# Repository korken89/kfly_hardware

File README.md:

# KFly v3 hardware

This is the hardware for https://github.com/korken89/kfly_firmware

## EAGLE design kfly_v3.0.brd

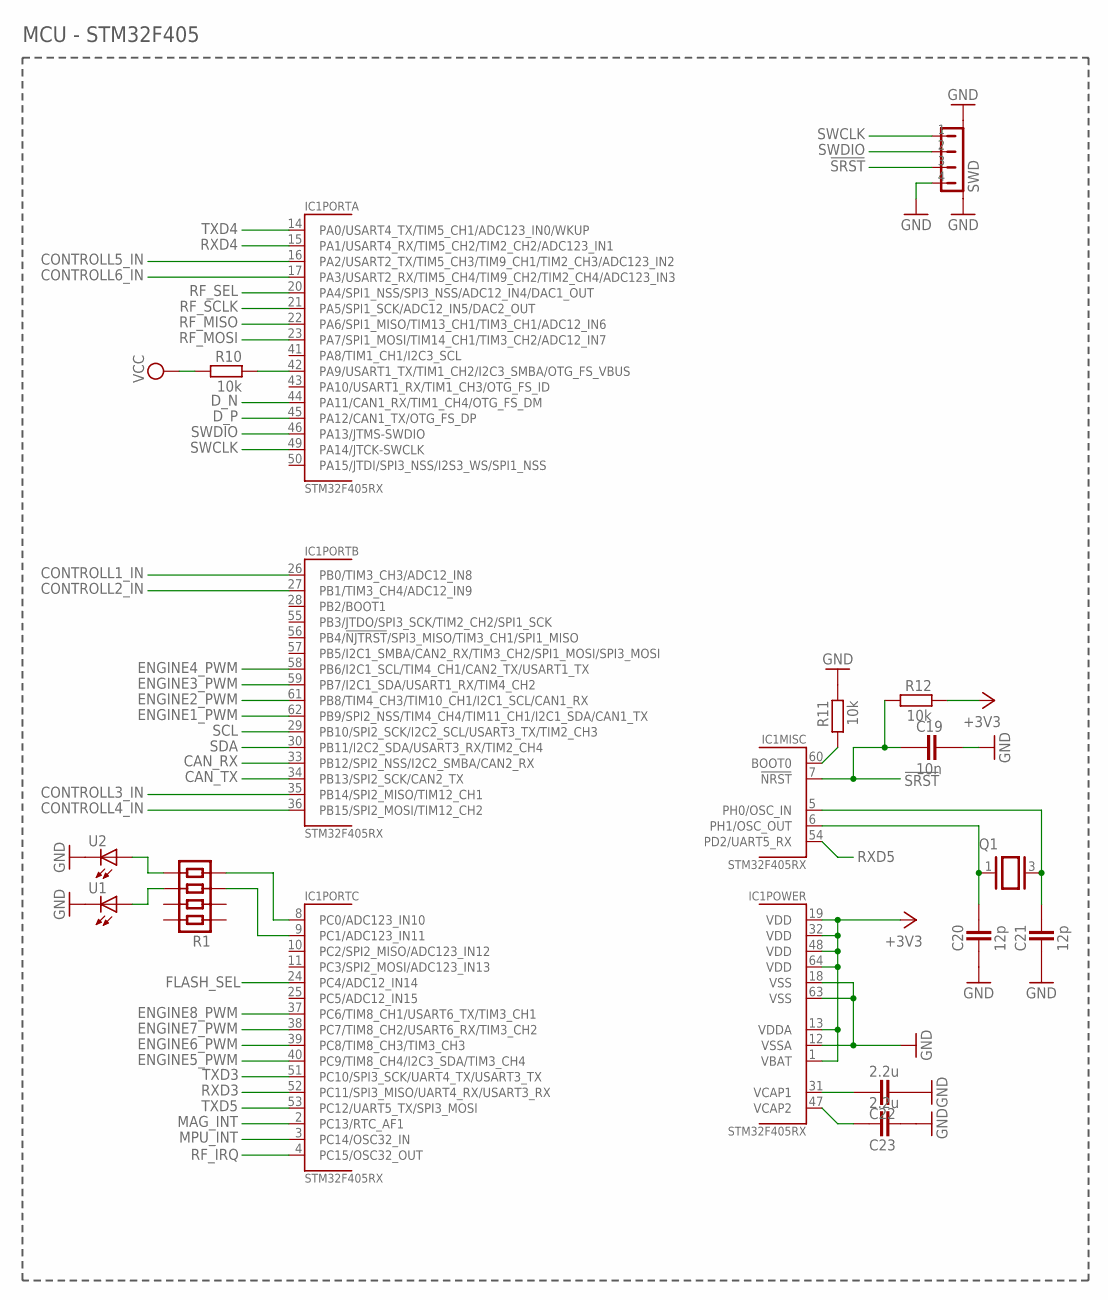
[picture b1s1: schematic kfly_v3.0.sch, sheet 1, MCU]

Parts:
C19: 10n; CAPC1005X60N
C20, C21: 12p; CAPC1005X60N
C22, C23: 2.2u; CAPC1608X92N
IC1: STM32F405RX; LQFP64-10X10
Q1: 2.5X3.2CRYSTAL
R1: RESISTOR-4ARRAY-0804; RESISTORARRAY_0804
R10, R11, R12: 10k; RESC1005X40AN
SWD: JST-4PIN-SIDE-1.0; JST-4PIN-SIDE
U1, U2: LED0603; LED-0603

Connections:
!SRST: C19.1, IC1.7 (!NRST!), R12.2, SWD.3
+3V3: IC1.1 (VBAT), IC1.13 (VDDA), IC1.19 (VDD), IC1.32 (VDD), IC1.48 (VDD), IC1.64 (VDD), R12.1; also elsewhere on the board
CAN_RX: IC1.33 (PB12/SPI2_NSS/I2C2_SMBA/CAN2_RX); also elsewhere on the board
CAN_TX: IC1.34 (PB13/SPI2_SCK/CAN2_TX); also elsewhere on the board
CONTROLL1_IN: IC1.26 (PB0/TIM3_CH3/ADC12_IN8); also elsewhere on the board
CONTROLL2_IN: IC1.27 (PB1/TIM3_CH4/ADC12_IN9); also elsewhere on the board
CONTROLL3_IN: IC1.35 (PB14/SPI2_MISO/TIM12_CH1); also elsewhere on the board
CONTROLL4_IN: IC1.36 (PB15/SPI2_MOSI/TIM12_CH2); also elsewhere on the board
CONTROLL5_IN: IC1.16 (PA2/USART2_TX/TIM5_CH3/TIM9_CH1/TIM2_CH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); also elsewhere on the board
CONTROLL6_IN: IC1.17 (PA3/USART2_RX/TIM5_CH4/TIM9_CH2/TIM2_CH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); also elsewhere on the board
D_N: IC1.44 (PA11/CAN1_RX/TIM1_CH4/OTG_FS_DM); also elsewhere on the board
D_P: IC1.45 (PA12/CAN1_TX/OTG_FS_DP); also elsewhere on the board
ENGINE1_PWM: IC1.62 (PB9/SPI2_NSS/TIM4_CH4/TIM11_CH1/I2C1_SD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); also elsewhere on the board
ENGINE2_PWM: IC1.61 (PB8/TIM4_CH3/TIM10_CH1/I2C1_SCL/CAN1_RX); also elsewhere on the board
ENGINE3_PWM: IC1.59 (PB7/I2C1_SDA/USART1_RX/TIM4_CH2); also elsewhere on the board
ENGINE4_PWM: IC1.58 (PB6/I2C1_SCL/TIM4_CH1/CAN2_TX/USART1_TX); also elsewhere on the board
ENGINE5_PWM: IC1.40 (PC9/TIM8_CH4/I2C3_SDA/TIM3_CH4); also elsewhere on the board
ENGINE6_PWM: IC1.39 (PC8/TIM8_CH3/TIM3_CH3); also elsewhere on the board
ENGINE7_PWM: IC1.38 (PC7/TIM8_CH2/USART6_RX/TIM3_CH2); also elsewhere on the board
ENGINE8_PWM: IC1.37 (PC6/TIM8_CH1/USART6_TX/TIM3_CH1); also elsewhere on the board
FLASH_SEL: IC1.24 (PC4/ADC12_IN14); also elsewhere on the board
GND: C19.2, C20.1, C21.1, C22.2, C23.2, IC1.12 (VSSA), IC1.18 (VSS), IC1.63 (VSS), R11.1, SWD.4, SWD.NC1 (P1), SWD.NC2 (P2), U1.C, U2.C; also elsewhere on the board
MAG_INT: IC1.2 (PC13/RTC_AF1); also elsewhere on the board
MPU_INT: IC1.3 (PC14/OSC32_IN); also elsewhere on the board
unnamed: R1.5, U2.A
unnamed: R1.6, U1.A
unnamed: IC1.60 (BOOT0), R11.2
unnamed: IC1.8 (PC0/ADC123_IN10), R1.4
unnamed: IC1.9 (PC1/ADC123_IN11), R1.3
unnamed: C20.2, IC1.6 (PH1/OSC_OUT), Q1.1
unnamed: C21.2, IC1.5 (PH0/OSC_IN), Q1.3 (2)
unnamed: IC1.42 (PA9/USART1_TX/TIM1_CH2/I2C3_SMBA/OTG_FS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), R10.1
unnamed: C22.1, IC1.31 (VCAP1)
unnamed: C23.1, IC1.47 (VCAP2)
RF_IRQ: IC1.4 (PC15/OSC32_OUT); also elsewhere on the board
RF_MISO: IC1.22 (PA6/SPI1_MISO/TIM13_CH1/TIM3_CH1/ADC12_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); also elsewhere on the board
RF_MOSI: IC1.23 (PA7/SPI1_MOSI/TIM14_CH1/TIM3_CH2/ADC12_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); also elsewhere on the board
RF_SCLK: IC1.21 (PA5/SPI1_SCK/ADC12_IN5/DAC2_OUT); also elsewhere on the board
RF_SEL: IC1.20 (PA4/SPI1_NSS/SPI3_NSS/ADC12_IN4/DAC1_OUT); also elsewhere on the board
RXD3: IC1.52 (PC11/SPI3_MISO/UART4_RX/USART3_RX); also elsewhere on the board
RXD4: IC1.15 (PA1/USART4_RX/TIM5_CH2/TIM2_CH2/ADC123_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); also elsewhere on the board
RXD5: IC1.54 (PD2/UART5_RX); also elsewhere on the board
SCL: IC1.29 (PB10/SPI2_SCK/I2C2_SCL/USART3_TX/TIM2_C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); also elsewhere on the board
SDA: IC1.30 (PB11/I2C2_SDA/USART3_RX/TIM2_CH4); also elsewhere on the board
SWCLK: IC1.49 (PA14/JTCK-SWCLK), SWD.1
SWDIO: IC1.46 (PA13/JTMS-SWDIO), SWD.2
TXD3: IC1.51 (PC10/SPI3_SCK/UART4_TX/USART3_TX); also elsewhere on the board
TXD4: IC1.14 (PA0/USART4_TX/TIM5_CH1/ADC123_IN0/WKUP); also elsewhere on the board
TXD5: IC1.53 (PC12/UART5_TX/SPI3_MOSI); also elsewhere on the board
VCC: R10.2; also elsewhere on the board

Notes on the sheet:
MCU - STM32F405

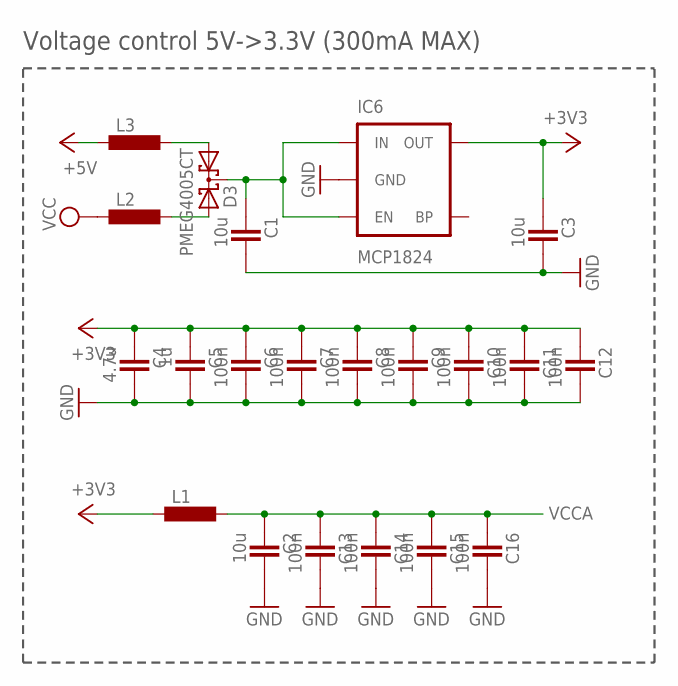
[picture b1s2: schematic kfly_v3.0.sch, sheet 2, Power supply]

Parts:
C1, C2, C3: 10u; CAPC1608X92N
C4: 4.7u; CAPC1608X92N
C5: 1u; CAPC1608X92N
C6, C7, C8, C9, C10, C11, C12, C13, C14, C15, C16: 100n; CAPC1005X60N
D3: PMEG4005CT; SOT23
IC6: MCP1824; SOT23-5
L1, L2, L3: INDUCTOR_0603; INDC1608X95N

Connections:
+3V3: C3.1, C4.1, C5.1, C6.1, C7.1, C8.1, C9.1, C10.1, C11.1, C12.1, IC6.5 (OUT), L1.1; also elsewhere on the board
+5V: L3.1; also elsewhere on the board
GND: C1.2, C2.2, C3.2, C4.2, C5.2, C6.2, C7.2, C8.2, C9.2, C10.2, C11.2, C12.2, C13.2, C14.2, C15.2, C16.2, IC6.2 (GND); also elsewhere on the board
unnamed: D3.2 (A2), L2.2
unnamed: D3.1 (A1), L3.2
VCC: L2.1; also elsewhere on the board
VCCA: C2.1, C13.1, C14.1, C15.1, C16.1, L1.2; also elsewhere on the board
V_RC: C1.1, D3.3 (C), IC6.1 (IN), IC6.3 (EN)

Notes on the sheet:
Voltage control 5V->3.3V (300mA MAX)

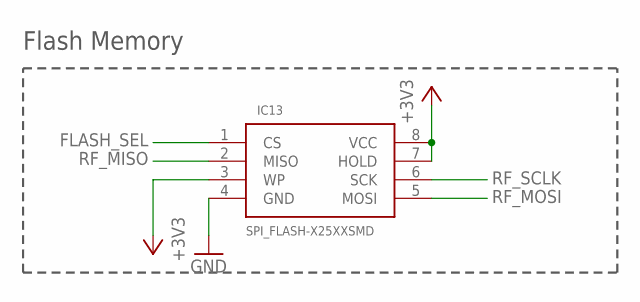
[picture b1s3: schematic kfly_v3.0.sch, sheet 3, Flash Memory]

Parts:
IC13: SPI_FLASH-X25XXSMD; SO08

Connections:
+3V3: IC13.3 (WP), IC13.7 (HOLD), IC13.8 (VCC); also elsewhere on the board
FLASH_SEL: IC13.1 (CS); also elsewhere on the board
GND: IC13.4 (GND); also elsewhere on the board
RF_MISO: IC13.2 (MISO); also elsewhere on the board
RF_MOSI: IC13.5 (MOSI); also elsewhere on the board
RF_SCLK: IC13.6 (SCK); also elsewhere on the board

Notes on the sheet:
Flash Memory

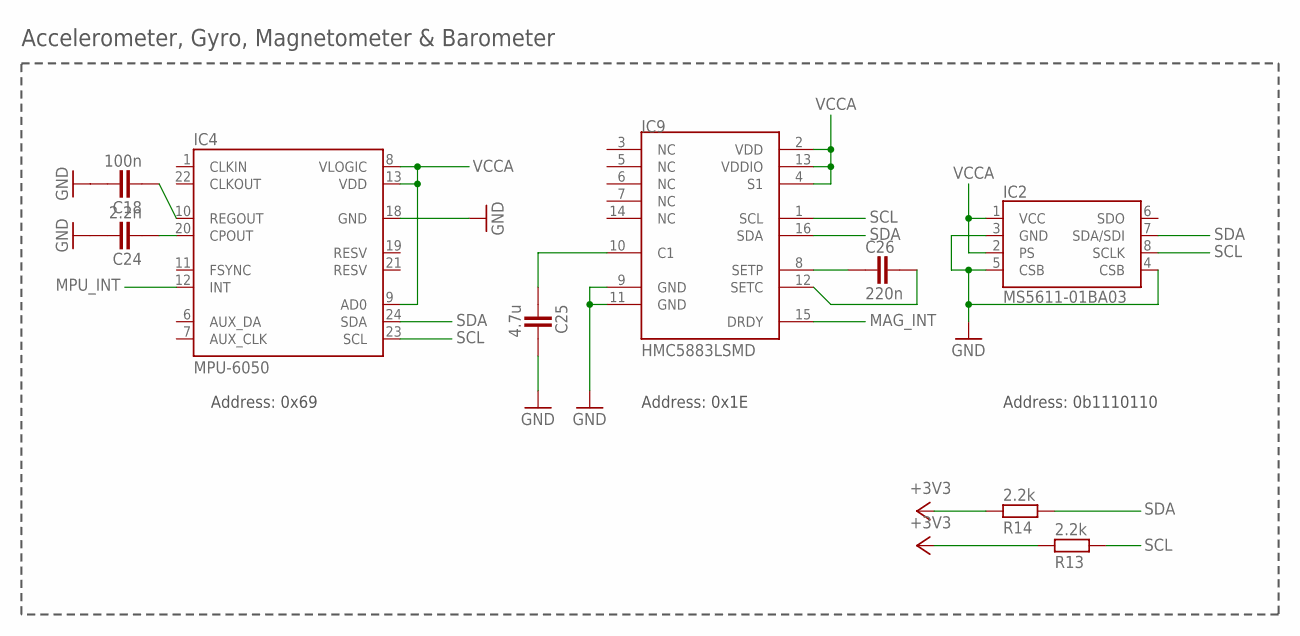
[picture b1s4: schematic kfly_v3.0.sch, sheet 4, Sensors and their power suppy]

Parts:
C18: 100n; CAPC1005X60N
C24: 2.2n; CAPC1005X60N
C25: 4.7u; CAPC1608X92N
C26: 220n; CAPC1608X92N
IC2: MS5611-01BA03; MS5611
IC4: MPU-6050; QFN-24
IC9: HMC5883LSMD; 16LPCC
R13, R14: 2.2k; RESC1005X40AN

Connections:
+3V3: R13.1, R14.1; also elsewhere on the board
GND: C18.2, C24.2, C25.2, IC2.3 (GND), IC2.4 (CSB), IC2.5 (CSB), IC4.18 (GND), IC9.9 (GND), IC9.11 (GND); also elsewhere on the board
MAG_INT: IC9.15 (DRDY); also elsewhere on the board
MPU_INT: IC4.12 (INT); also elsewhere on the board
unnamed: C25.1, IC9.10 (C1)
unnamed: C26.1, IC9.8 (SETP)
unnamed: C26.2, IC9.12 (SETC)
unnamed: C18.1, IC4.10 (REGOUT)
unnamed: C24.1, IC4.20 (CPOUT)
SCL: IC2.8 (SCLK), IC4.23 (SCL), IC9.1 (SCL), R13.2; also elsewhere on the board
SDA: IC2.7 (SDA/SDI), IC4.24 (SDA), IC9.16 (SDA), R14.2; also elsewhere on the board
VCCA: IC2.1 (VCC), IC2.2 (PS), IC4.8 (VLOGIC), IC4.9 (AD0), IC4.13 (VDD), IC9.2 (VDD), IC9.4 (S1), IC9.13 (VDDIO); also elsewhere on the board

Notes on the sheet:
Accelerometer, Gyro, Magnetometer & Barometer
Address: 0x69
Address: 0x1E
Address: 0b1110110

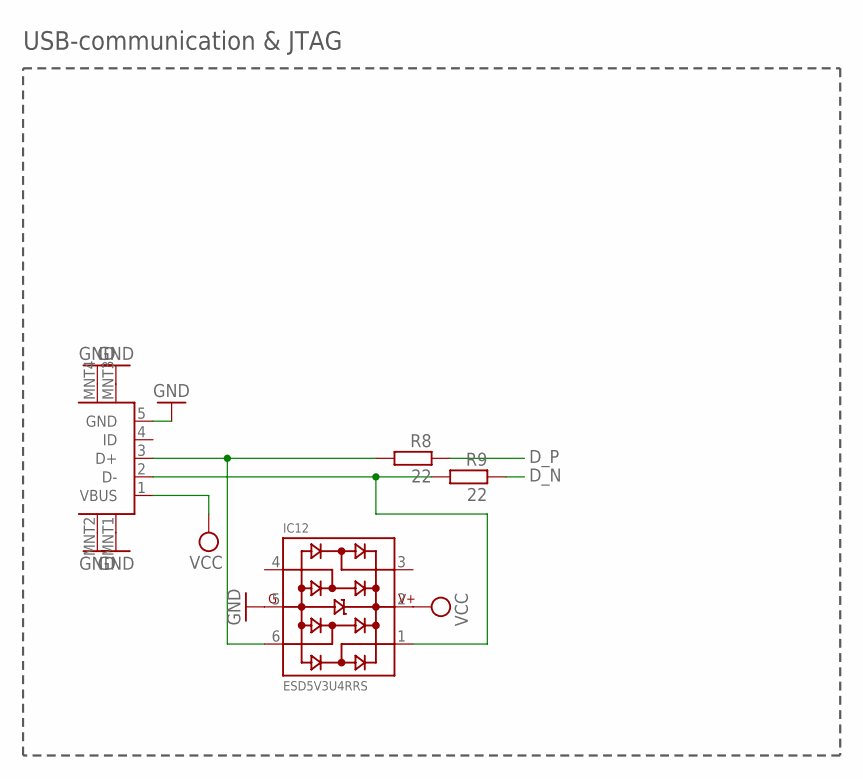
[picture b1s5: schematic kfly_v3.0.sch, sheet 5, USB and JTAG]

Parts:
IC12: ESD5V3U4RRS; SOT363
R8, R9: 22; RESC1005X40AN
USB1: USB-MICRO-B-BOTTOM; MICROUSB_TYPEB_SURFACE

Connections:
D_N: R9.1; also elsewhere on the board
D_P: R8.1; also elsewhere on the board
GND: IC12.5, USB1.5 (GND), USB1.MNT1 (MTN1), USB1.MNT2 (MTN2), USB1.MNT3 (MTN3), USB1.MNT4 (MTN4); also elsewhere on the board
unnamed: IC12.6, R8.2, USB1.3 (D+)
unnamed: IC12.1, R9.2, USB1.2 (D-)
VCC: IC12.2, USB1.1 (VBUS); also elsewhere on the board

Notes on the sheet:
USB-communication & JTAG

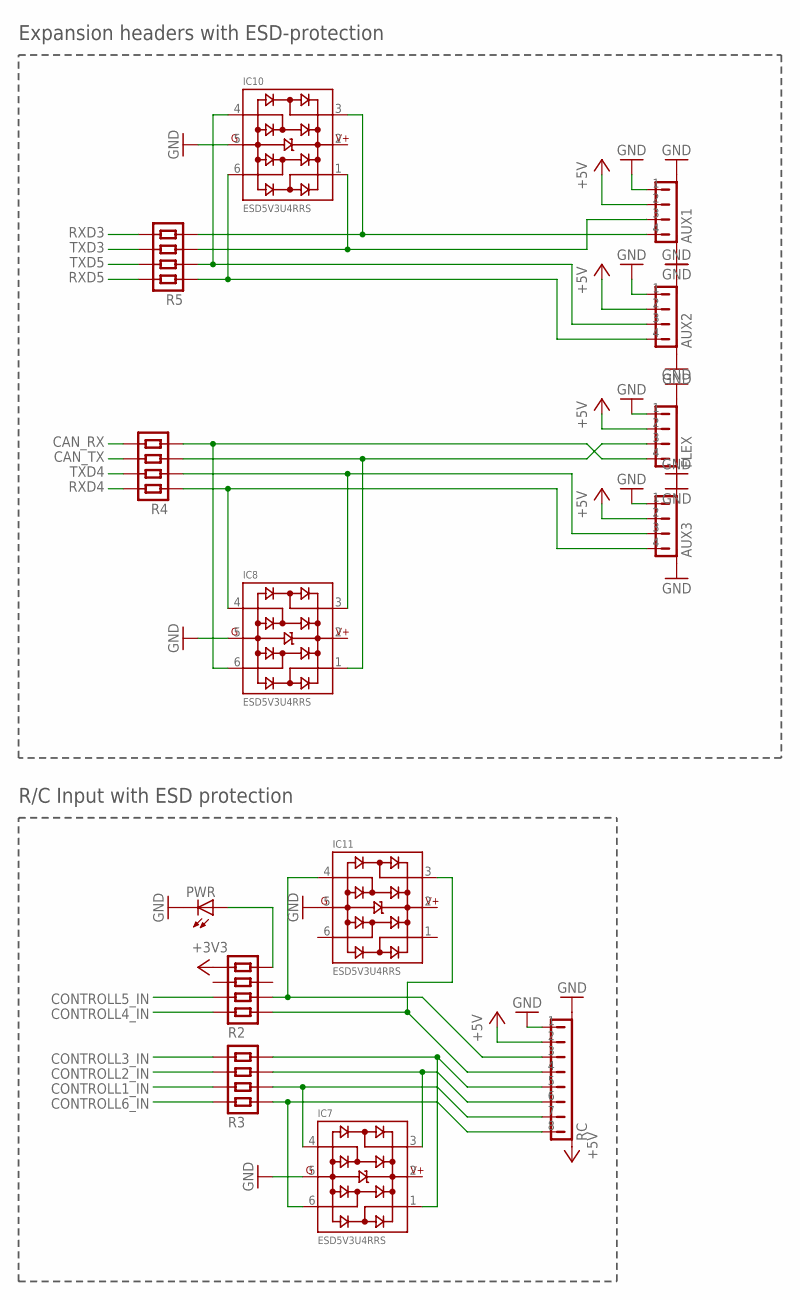
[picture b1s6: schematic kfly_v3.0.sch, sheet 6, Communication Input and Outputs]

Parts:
AUX1, AUX2, AUX3: JST-4PIN-SIDE-1.0; JST-4PIN-SIDE
FLEX: JST-4PIN-SIDE-1.0; JST-4PIN-SIDE
IC7, IC8, IC10, IC11: ESD5V3U4RRS; SOT363
PWR: LED0603; LED-0603
R2, R3, R4, R5: RESISTOR-4ARRAY-0804; RESISTORARRAY_0804
RC: JST-8PIN-SIDE-1.0; JST-8PIN-SIDE

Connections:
+3V3: R2.4; also elsewhere on the board
+5V: AUX1.2, AUX2.2, AUX3.2, FLEX.2, RC.2, RC.NC2 (GND2); also elsewhere on the board
CAN_RX: R4.5; also elsewhere on the board
CAN_TX: R4.6; also elsewhere on the board
CONTROLL1_IN: R3.2; also elsewhere on the board
CONTROLL2_IN: R3.3; also elsewhere on the board
CONTROLL3_IN: R3.4; also elsewhere on the board
CONTROLL4_IN: R2.1; also elsewhere on the board
CONTROLL5_IN: R2.2; also elsewhere on the board
CONTROLL6_IN: R3.1; also elsewhere on the board
GND: AUX1.1, AUX1.NC1 (P1), AUX1.NC2 (P2), AUX2.1, AUX2.NC1 (P1), AUX2.NC2 (P2), AUX3.1, AUX3.NC1 (P1), AUX3.NC2 (P2), FLEX.1, FLEX.NC1 (P1), FLEX.NC2 (P2), IC7.5, IC8.5, IC10.5, IC11.5, PWR.C, RC.1, RC.NC1 (GND1); also elsewhere on the board
unnamed: AUX2.3, IC10.4, R5.2
unnamed: PWR.A, R2.5
unnamed: IC11.4, R2.7, RC.3
unnamed: IC7.6, R3.8, RC.8
unnamed: IC7.1, R3.5, RC.5
unnamed: FLEX.4, IC8.6, R4.4
unnamed: FLEX.3, IC8.1, R4.3
unnamed: AUX2.4, IC10.6, R5.1
unnamed: IC11.3, R2.8, RC.4
unnamed: IC7.3, R3.6, RC.6
unnamed: AUX1.4, IC10.3, R5.4
unnamed: AUX1.3, IC10.1, R5.3
unnamed: AUX3.4, IC8.4, R4.1
unnamed: AUX3.3, IC8.3, R4.2
unnamed: IC7.4, R3.7, RC.7
RXD3: R5.5; also elsewhere on the board
RXD4: R4.8; also elsewhere on the board
RXD5: R5.8; also elsewhere on the board
TXD3: R5.6; also elsewhere on the board
TXD4: R4.7; also elsewhere on the board
TXD5: R5.7; also elsewhere on the board

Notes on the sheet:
Expansion headers with ESD-protection
R/C Input with ESD protection

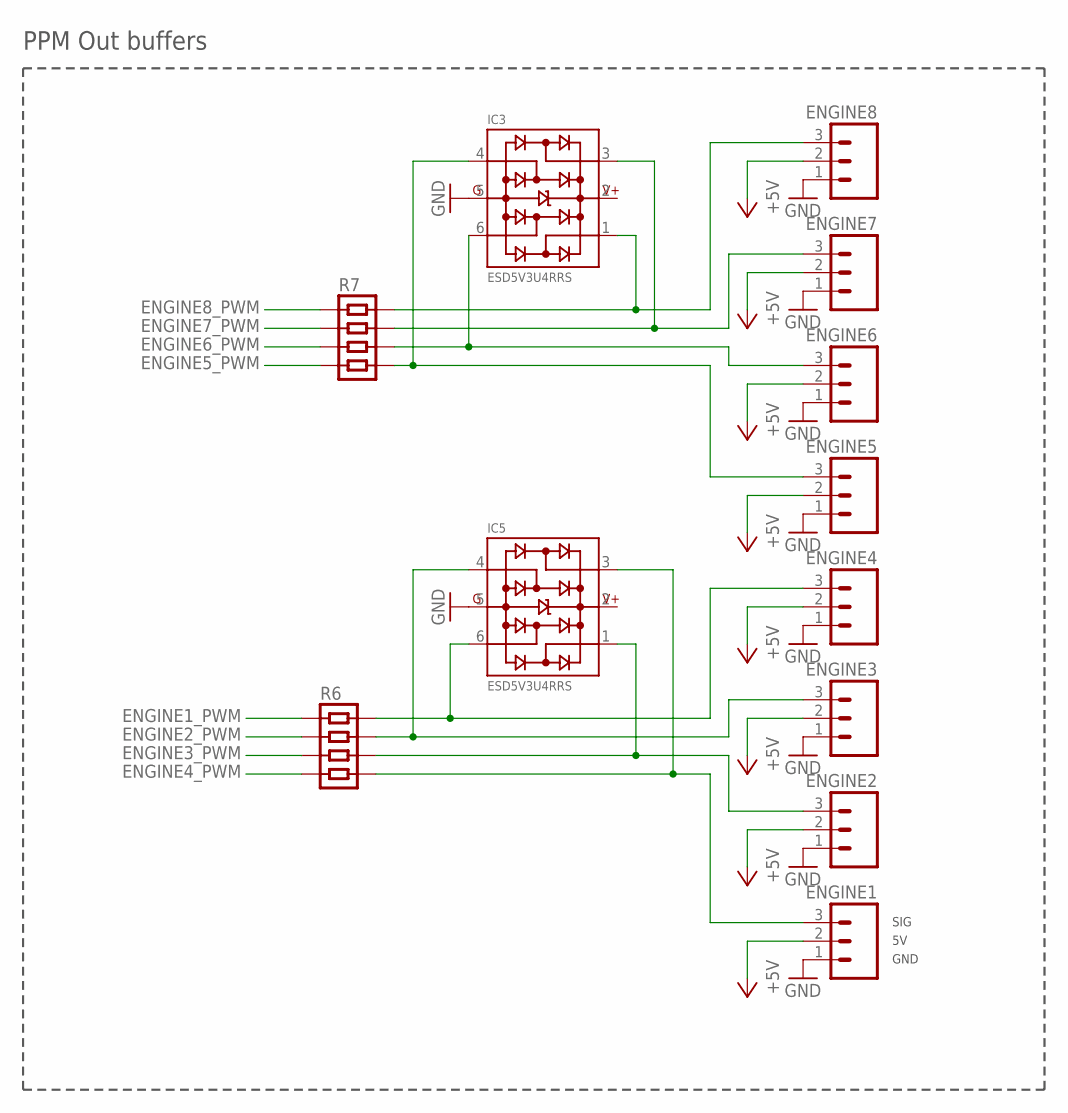
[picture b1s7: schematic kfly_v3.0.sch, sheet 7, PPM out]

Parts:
ENGINE1, ENGINE2, ENGINE3, ENGINE4, ENGINE5, ENGINE6, ENGINE7, ENGINE8: M03
IC3, IC5: ESD5V3U4RRS; SOT363
R6, R7: RESISTOR-4ARRAY-0804; RESISTORARRAY_0804

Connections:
+5V: ENGINE1.2, ENGINE2.2, ENGINE3.2, ENGINE4.2, ENGINE5.2, ENGINE6.2, ENGINE7.2, ENGINE8.2; also elsewhere on the board
ENGINE1_PWM: R6.1; also elsewhere on the board
ENGINE2_PWM: R6.2; also elsewhere on the board
ENGINE3_PWM: R6.3; also elsewhere on the board
ENGINE4_PWM: R6.4; also elsewhere on the board
ENGINE5_PWM: R7.4; also elsewhere on the board
ENGINE6_PWM: R7.3; also elsewhere on the board
ENGINE7_PWM: R7.2; also elsewhere on the board
ENGINE8_PWM: R7.1; also elsewhere on the board
GND: ENGINE1.1, ENGINE2.1, ENGINE3.1, ENGINE4.1, ENGINE5.1, ENGINE6.1, ENGINE7.1, ENGINE8.1, IC3.5, IC5.5; also elsewhere on the board
unnamed: ENGINE8.3, IC3.1, R7.8
unnamed: ENGINE7.3, IC3.3, R7.7
unnamed: ENGINE6.3, IC3.6, R7.6
unnamed: ENGINE5.3, IC3.4, R7.5
unnamed: ENGINE2.3, IC5.1, R6.6
unnamed: ENGINE1.3, IC5.3, R6.5
unnamed: ENGINE4.3, IC5.6, R6.8
unnamed: ENGINE3.3, IC5.4, R6.7

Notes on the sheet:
PPM Out buffers
GND
SIG

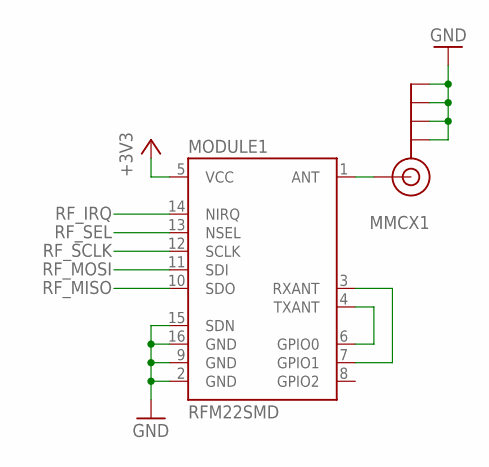
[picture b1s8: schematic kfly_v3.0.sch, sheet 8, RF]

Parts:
MMCX1: MMCX; MMCX_THROUGHHOLE_RIGHTANGLE
MODULE1: RFM22SMD; RFM22-XXX-S2

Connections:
+3V3: MODULE1.5 (VCC); also elsewhere on the board
GND: MMCX1.G1 (GND), MMCX1.G2 (GND), MMCX1.G3 (GND), MMCX1.G4 (GND), MODULE1.2 (GND), MODULE1.9 (GND), MODULE1.15 (SDN), MODULE1.16 (GND); also elsewhere on the board
unnamed: MMCX1.S (SIGNAL), MODULE1.1 (ANT)
unnamed: MODULE1.4 (TXANT), MODULE1.6 (GPIO0)
unnamed: MODULE1.3 (RXANT), MODULE1.7 (GPIO1)
RF_IRQ: MODULE1.14 (NIRQ); also elsewhere on the board
RF_MISO: MODULE1.10 (SDO); also elsewhere on the board
RF_MOSI: MODULE1.11 (SDI); also elsewhere on the board
RF_SCLK: MODULE1.12 (SCLK); also elsewhere on the board
RF_SEL: MODULE1.13 (NSEL); also elsewhere on the board

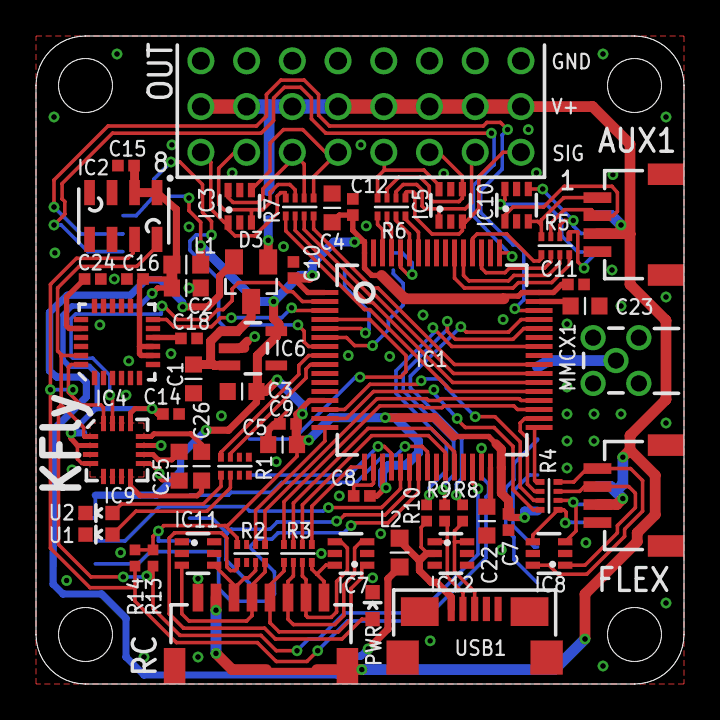
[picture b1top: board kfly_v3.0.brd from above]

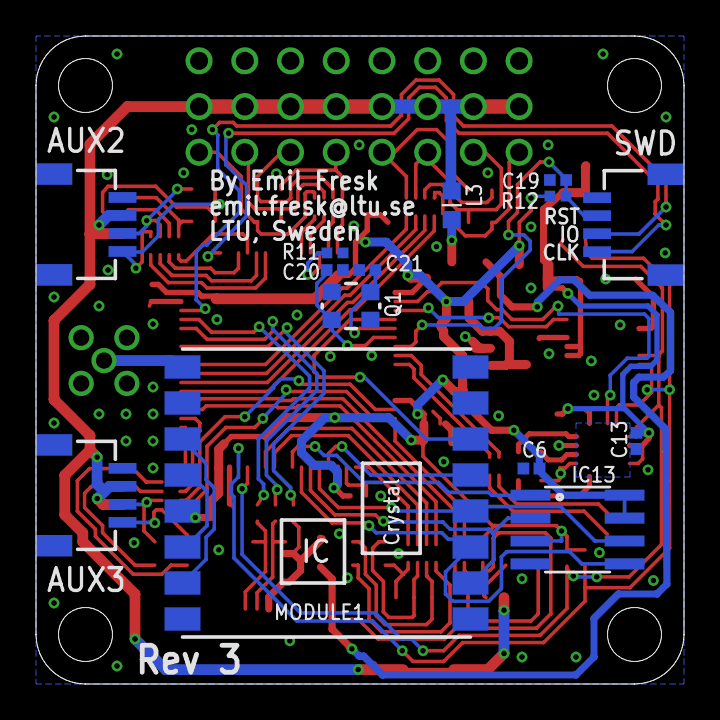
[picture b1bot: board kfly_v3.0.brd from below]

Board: 4 copper layers, 36.0 x 36.0 mm, 77 parts (14 on the bottom side), 88 nets.

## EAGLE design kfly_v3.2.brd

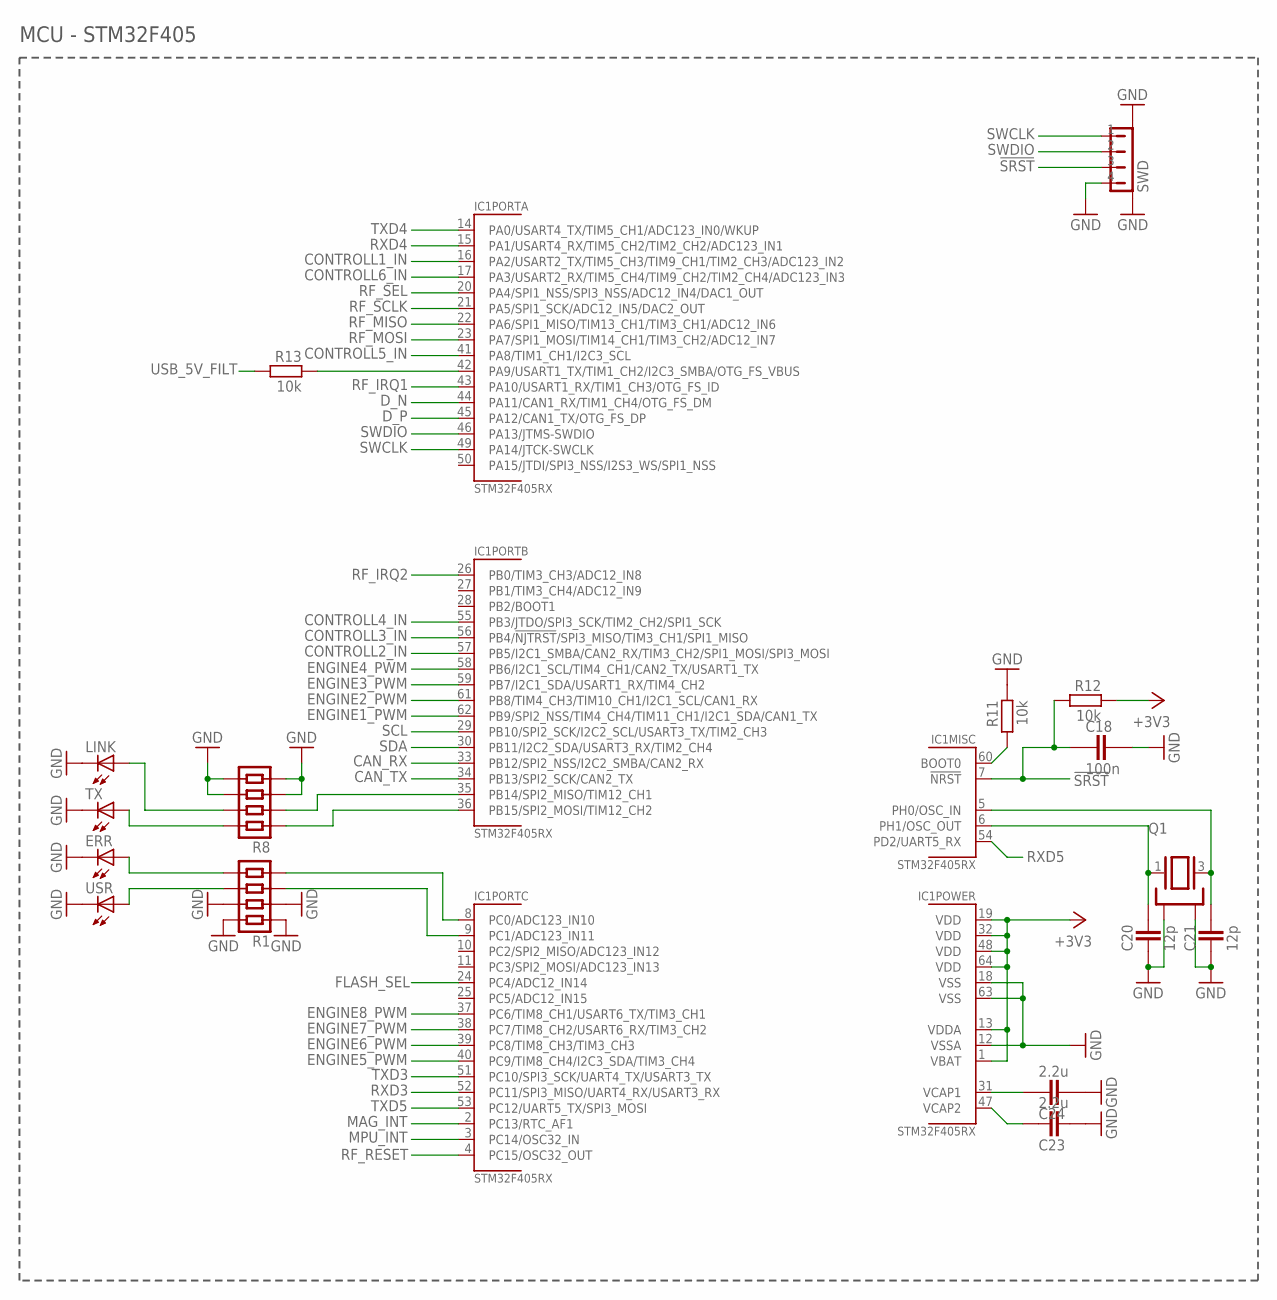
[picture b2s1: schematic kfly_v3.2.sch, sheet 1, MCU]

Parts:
C18: 100n; CAPC1005X60N
C20, C21: 12p; CAPC1005X60N
C23, C24: 2.2u; CAPC1005X60N
ERR: LED0603; LED-0603
IC1: STM32F405RX; LQFP64-10X10
LINK: LED0603; LED-0603
Q1: 2.5X3.2CRYSTAL
R1, R8: RESISTOR-4ARRAY-0804; RESISTORARRAY_0804
R11, R12, R13: 10k; RESC1005X40AN
SWD: JST-4PIN-SIDE-1.0; JST-4PIN-SIDE
TX: LED0603; LED-0603
USR: LED0603; LED-0603

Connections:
!SRST: C18.1, IC1.7 (!NRST!), R12.2, SWD.3
+3V3: IC1.1 (VBAT), IC1.13 (VDDA), IC1.19 (VDD), IC1.32 (VDD), IC1.48 (VDD), IC1.64 (VDD), R12.1; also elsewhere on the board
CAN_RX: IC1.33 (PB12/SPI2_NSS/I2C2_SMBA/CAN2_RX); also elsewhere on the board
CAN_TX: IC1.34 (PB13/SPI2_SCK/CAN2_TX); also elsewhere on the board
CONTROLL1_IN: IC1.16 (PA2/USART2_TX/TIM5_CH3/TIM9_CH1/TIM2_CH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); also elsewhere on the board
CONTROLL2_IN: IC1.57 (PB5/I2C1_SMBA/CAN2_RX/TIM3_CH2/SPI1_MOS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); also elsewhere on the board
CONTROLL3_IN: IC1.56 (PB4/!NJTRST!/SPI3_MISO/TIM3_CH1/SPI1_MI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); also elsewhere on the board
CONTROLL4_IN: IC1.55 (PB3/JTDO/SPI3_SCK/TIM2_CH2/SPI1_SCK); also elsewhere on the board
CONTROLL5_IN: IC1.41 (PA8/TIM1_CH1/I2C3_SCL); also elsewhere on the board
CONTROLL6_IN: IC1.17 (PA3/USART2_RX/TIM5_CH4/TIM9_CH2/TIM2_CH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); also elsewhere on the board
D_N: IC1.44 (PA11/CAN1_RX/TIM1_CH4/OTG_FS_DM); also elsewhere on the board
D_P: IC1.45 (PA12/CAN1_TX/OTG_FS_DP); also elsewhere on the board
ENGINE1_PWM: IC1.62 (PB9/SPI2_NSS/TIM4_CH4/TIM11_CH1/I2C1_SD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); also elsewhere on the board
ENGINE2_PWM: IC1.61 (PB8/TIM4_CH3/TIM10_CH1/I2C1_SCL/CAN1_RX); also elsewhere on the board
ENGINE3_PWM: IC1.59 (PB7/I2C1_SDA/USART1_RX/TIM4_CH2); also elsewhere on the board
ENGINE4_PWM: IC1.58 (PB6/I2C1_SCL/TIM4_CH1/CAN2_TX/USART1_TX); also elsewhere on the board
ENGINE5_PWM: IC1.40 (PC9/TIM8_CH4/I2C3_SDA/TIM3_CH4); also elsewhere on the board
ENGINE6_PWM: IC1.39 (PC8/TIM8_CH3/TIM3_CH3); also elsewhere on the board
ENGINE7_PWM: IC1.38 (PC7/TIM8_CH2/USART6_RX/TIM3_CH2); also elsewhere on the board
ENGINE8_PWM: IC1.37 (PC6/TIM8_CH1/USART6_TX/TIM3_CH1); also elsewhere on the board
FLASH_SEL: IC1.24 (PC4/ADC12_IN14); also elsewhere on the board
GND: C18.2, C20.1, C21.1, C23.2, C24.2, ERR.C, IC1.12 (VSSA), IC1.18 (VSS), IC1.63 (VSS), LINK.C, Q1.2, Q1.4, R1.1, R1.2, R1.7, R1.8, R8.3, R8.4, R8.5, R8.6, R11.1, SWD.4, SWD.NC1 (P1), SWD.NC2 (P2), TX.C, USR.C; also elsewhere on the board
MAG_INT: IC1.2 (PC13/RTC_AF1); also elsewhere on the board
MPU_INT: IC1.3 (PC14/OSC32_IN); also elsewhere on the board
unnamed: ERR.A, R1.5
unnamed: IC1.35 (PB14/SPI2_MISO/TIM12_CH1), R8.2
unnamed: R1.6, USR.A
unnamed: IC1.60 (BOOT0), R11.2
unnamed: IC1.8 (PC0/ADC123_IN10), R1.4
unnamed: IC1.36 (PB15/SPI2_MOSI/TIM12_CH2), R8.1
unnamed: IC1.9 (PC1/ADC123_IN11), R1.3
unnamed: C20.2, IC1.6 (PH1/OSC_OUT), Q1.1
unnamed: C21.2, IC1.5 (PH0/OSC_IN), Q1.3 (2)
unnamed: IC1.42 (PA9/USART1_TX/TIM1_CH2/I2C3_SMBA/OTG_FS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), R13.1
unnamed: R8.8, TX.A
unnamed: LINK.A, R8.7
unnamed: C24.1, IC1.31 (VCAP1)
unnamed: C23.1, IC1.47 (VCAP2)
RF_IRQ1: IC1.43 (PA10/USART1_RX/TIM1_CH3/OTG_FS_ID); also elsewhere on the board
RF_IRQ2: IC1.26 (PB0/TIM3_CH3/ADC12_IN8); also elsewhere on the board
RF_MISO: IC1.22 (PA6/SPI1_MISO/TIM13_CH1/TIM3_CH1/ADC12_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); also elsewhere on the board
RF_MOSI: IC1.23 (PA7/SPI1_MOSI/TIM14_CH1/TIM3_CH2/ADC12_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); also elsewhere on the board
RF_RESET: IC1.4 (PC15/OSC32_OUT); also elsewhere on the board
RF_SCLK: IC1.21 (PA5/SPI1_SCK/ADC12_IN5/DAC2_OUT); also elsewhere on the board
RF_SEL: IC1.20 (PA4/SPI1_NSS/SPI3_NSS/ADC12_IN4/DAC1_OUT); also elsewhere on the board
RXD3: IC1.52 (PC11/SPI3_MISO/UART4_RX/USART3_RX); also elsewhere on the board
RXD4: IC1.15 (PA1/USART4_RX/TIM5_CH2/TIM2_CH2/ADC123_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); also elsewhere on the board
RXD5: IC1.54 (PD2/UART5_RX); also elsewhere on the board
SCL: IC1.29 (PB10/SPI2_SCK/I2C2_SCL/USART3_TX/TIM2_C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); also elsewhere on the board
SDA: IC1.30 (PB11/I2C2_SDA/USART3_RX/TIM2_CH4); also elsewhere on the board
SWCLK: IC1.49 (PA14/JTCK-SWCLK), SWD.1
SWDIO: IC1.46 (PA13/JTMS-SWDIO), SWD.2
TXD3: IC1.51 (PC10/SPI3_SCK/UART4_TX/USART3_TX); also elsewhere on the board
TXD4: IC1.14 (PA0/USART4_TX/TIM5_CH1/ADC123_IN0/WKUP); also elsewhere on the board
TXD5: IC1.53 (PC12/UART5_TX/SPI3_MOSI); also elsewhere on the board
USB_5V_FILT: R13.2; also elsewhere on the board

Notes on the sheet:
MCU - STM32F405

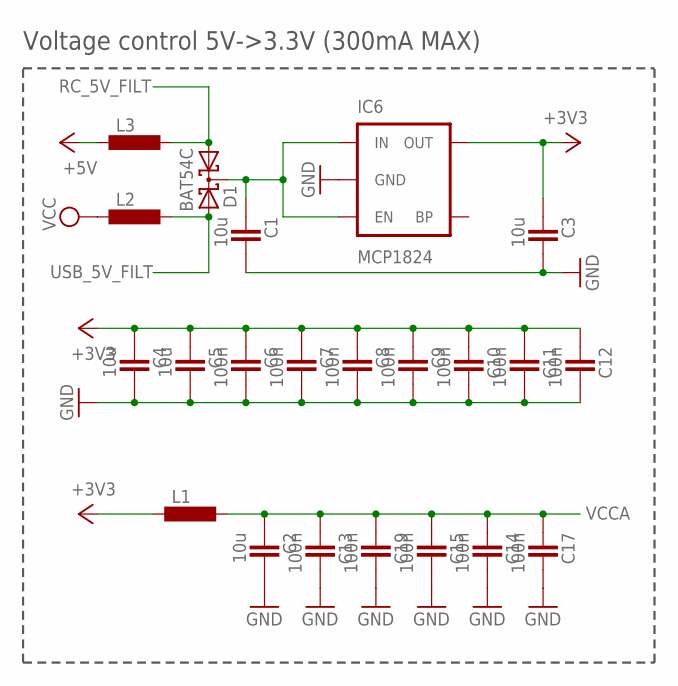
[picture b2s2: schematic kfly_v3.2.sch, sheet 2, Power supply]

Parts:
C1, C2, C3, C4, C5: 10u; CAPC1608X92N
C6, C7, C8, C9, C10, C11, C12, C13, C14, C15, C17, C19: 100n; CAPC1005X60N
D1: BAT54C; SOT23
IC6: MCP1824; SOT23-5
L1, L2, L3: INDUCTOR_0603; INDC1608X95N

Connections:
+3V3: C3.1, C4.1, C5.1, C6.1, C7.1, C8.1, C9.1, C10.1, C11.1, C12.1, IC6.5 (OUT), L1.1; also elsewhere on the board
+5V: L3.1; also elsewhere on the board
GND: C1.2, C2.2, C3.2, C4.2, C5.2, C6.2, C7.2, C8.2, C9.2, C10.2, C11.2, C12.2, C13.2, C14.2, C15.2, C17.2, C19.2, IC6.2 (GND); also elsewhere on the board
RC_5V_FILT: D1.1 (A1), L3.2; also elsewhere on the board
USB_5V_FILT: D1.2 (A2), L2.2; also elsewhere on the board
VCC: L2.1; also elsewhere on the board
VCCA: C2.1, C13.1, C14.1, C15.1, C17.1, C19.1, L1.2; also elsewhere on the board
V_RC: C1.1, D1.3 (CC), IC6.1 (IN), IC6.3 (EN)

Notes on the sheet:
Voltage control 5V->3.3V (300mA MAX)

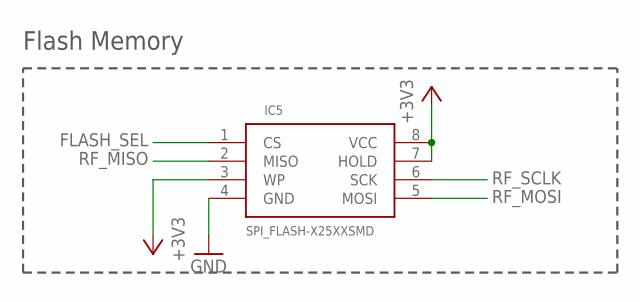
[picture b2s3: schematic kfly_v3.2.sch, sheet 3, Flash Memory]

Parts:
IC5: SPI_FLASH-X25XXSMD; SO08

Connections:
+3V3: IC5.3 (WP), IC5.7 (HOLD), IC5.8 (VCC); also elsewhere on the board
FLASH_SEL: IC5.1 (CS); also elsewhere on the board
GND: IC5.4 (GND); also elsewhere on the board
RF_MISO: IC5.2 (MISO); also elsewhere on the board
RF_MOSI: IC5.5 (MOSI); also elsewhere on the board
RF_SCLK: IC5.6 (SCK); also elsewhere on the board

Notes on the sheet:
Flash Memory

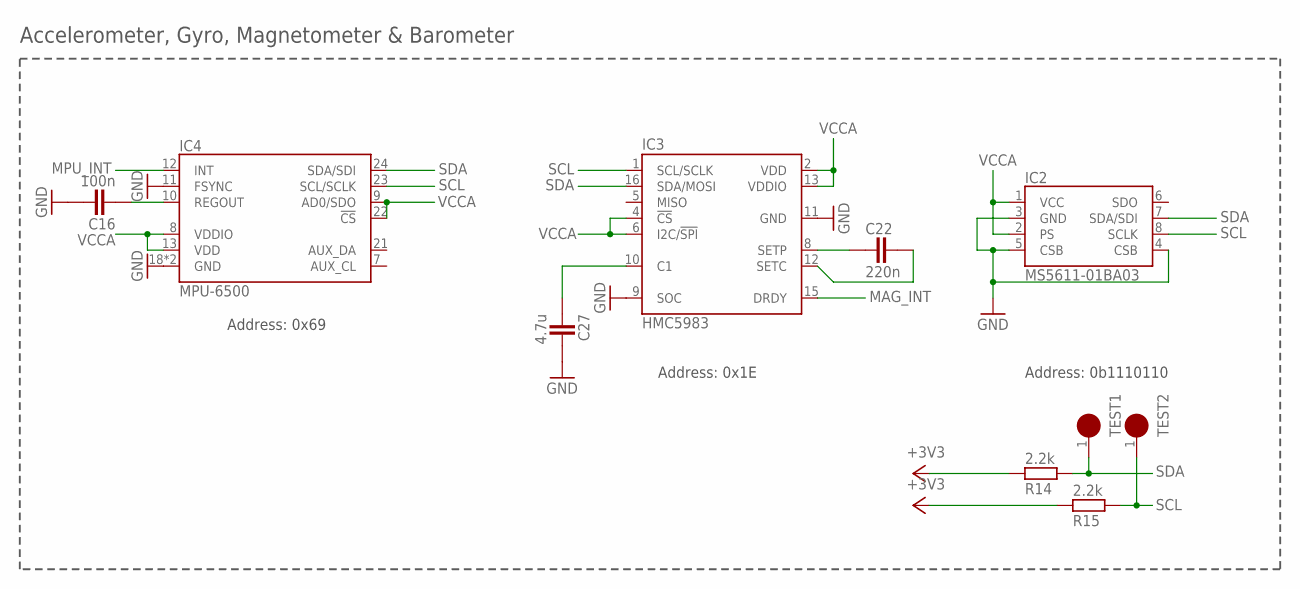
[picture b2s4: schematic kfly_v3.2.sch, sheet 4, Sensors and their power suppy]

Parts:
C16: 100n; CAPC1005X60N
C22: 220n; CAPC1608X92N
C27: 4.7u; CAPC1608X92N
IC2: MS5611-01BA03; MS5611
IC3: HMC5983; LPCC16
IC4: MPU-6500; QFN-24-3X3MM
R14, R15: 2.2k; RESC1005X40AN
TEST1, TEST2: TESTPOINT; TESTPOINT_1.2

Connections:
+3V3: R14.1, R15.1; also elsewhere on the board
GND: C16.2, C27.2, IC2.3 (GND), IC2.4 (CSB), IC2.5 (CSB), IC3.9 (SOC), IC3.11 (GND), IC4.11 (FSYNC), IC4.18 (GND), IC4.20 (GND); also elsewhere on the board
MAG_INT: IC3.15 (DRDY); also elsewhere on the board
MPU_INT: IC4.12 (INT); also elsewhere on the board
unnamed: C27.1, IC3.10 (C1)
unnamed: C22.1, IC3.8 (SETP)
unnamed: C22.2, IC3.12 (SETC)
unnamed: C16.1, IC4.10 (REGOUT)
SCL: IC2.8 (SCLK), IC3.1 (SCL/SCLK), IC4.23 (SCL/SCLK), R15.2, TEST2.1; also elsewhere on the board
SDA: IC2.7 (SDA/SDI), IC3.16 (SDA/MOSI), IC4.24 (SDA/SDI), R14.2, TEST1.1; also elsewhere on the board
VCCA: IC2.1 (VCC), IC2.2 (PS), IC3.2 (VDD), IC3.4 (!CS), IC3.6 (I2C/!SPI), IC3.13 (VDDIO), IC4.8 (VDDIO), IC4.9 (AD0/SDO), IC4.13 (VDD), IC4.22 (!CS); also elsewhere on the board

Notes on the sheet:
Accelerometer, Gyro, Magnetometer & Barometer
Address: 0x69
Address: 0x1E
Address: 0b1110110

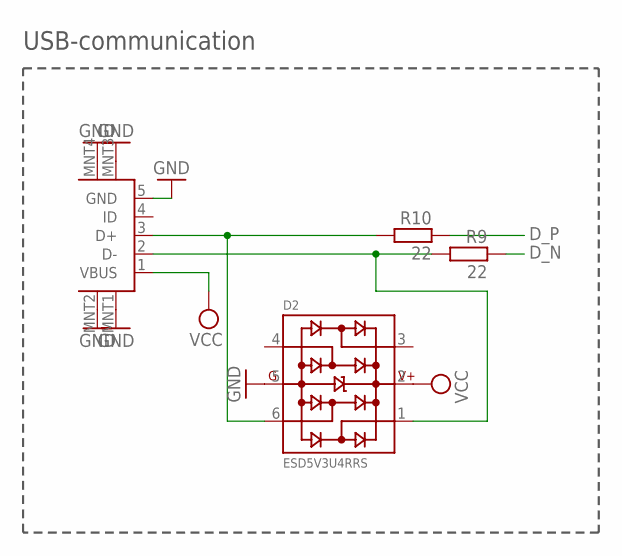
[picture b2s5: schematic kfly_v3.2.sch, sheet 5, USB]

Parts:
D2: ESD5V3U4RRS; SOT363
R9, R10: 22; RESC1005X40AN
USB1: USB-MICRO-B-BOTTOM; MICROUSB_TYPEB_SURFACE

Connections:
D_N: R9.1; also elsewhere on the board
D_P: R10.1; also elsewhere on the board
GND: D2.5, USB1.5 (GND), USB1.MNT1 (MTN1), USB1.MNT2 (MTN2), USB1.MNT3 (MTN3), USB1.MNT4 (MTN4); also elsewhere on the board
unnamed: D2.6, R10.2, USB1.3 (D+)
unnamed: D2.1, R9.2, USB1.2 (D-)
VCC: D2.2, USB1.1 (VBUS); also elsewhere on the board

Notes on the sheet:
USB-communication
